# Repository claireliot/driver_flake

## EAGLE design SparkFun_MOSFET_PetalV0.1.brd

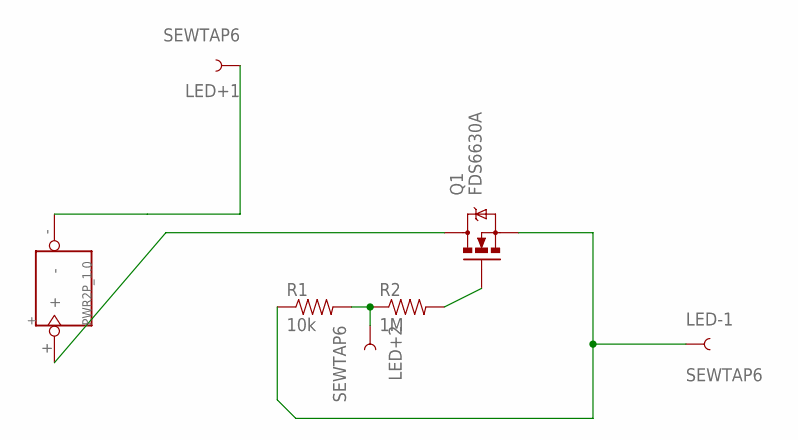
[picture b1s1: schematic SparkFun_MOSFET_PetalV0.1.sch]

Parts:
+: PWR2P_1.0
LED+1, LED+2: SEWTAP6; PETAL-SMALL-2SIDE
LED-1: SEWTAP6; PETAL-SMALL-2SIDE
Q1: FDS6630A; SO08
R1: 10k; 0402-RES
R2: 1M; 0402-RES

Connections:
GND: LED-1.1, Q1.1 (S), Q1.2 (S), Q1.3 (S), R1.1
unnamed: Q1.4 (G), R2.2
unnamed: +.-, LED+1.1
unnamed: LED+2.1, R1.2, R2.1
unnamed: +.+, Q1.5 (D), Q1.6 (D), Q1.7 (D), Q1.8 (D)

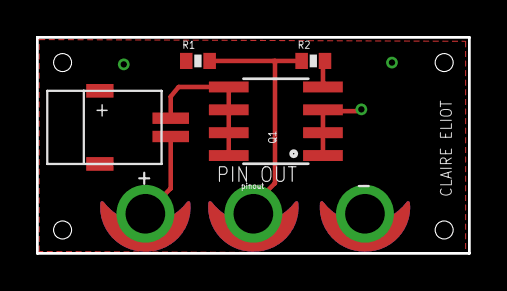
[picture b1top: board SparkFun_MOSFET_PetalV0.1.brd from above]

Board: 2 copper layers, 24.0 x 12.0 mm, 7 parts (0 on the bottom side), 5 nets.

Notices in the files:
parts and their libraries:
SparkFun-Passives: Licensing: CC v3.0 Share-Alike You are welcome to use this library for commercial purposes.
LilyPad-Wearables: Licensing:Creative Commons ShareAlike 4.0 International - https://creativecommons.org/licenses/by-sa/4.0
